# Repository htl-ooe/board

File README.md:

# HTL OOE HAT for Raspberry Pi
board schematic, layout and instructions on how to operate the board

## Installing the Operating System

### Downloading the Operating System
There are lots of operating Systems (Distributions) for the Raspberry Pi. Most of them are based on Linux.
The Foundation’s official supported operating system is [Raspberry Pi OS](https://www.raspberrypi.org/downloads/raspberry-pi-os/ "Raspberry Pi OS").
There are 3 Variants:
  * [Raspberry Pi OS with desktop and recommended software](https://downloads.raspberrypi.org/raspios_full_armhf_latest "Raspberry Pi OS full")
  * [Raspberry Pi OS with desktop](https://downloads.raspberrypi.org/raspios_armhf_latest "Raspberry Pi OS with Desktop")
  * [Raspberry Pi OS Lite (just Console, smallest in size)](hhttps://downloads.raspberrypi.org/raspios_lite_armhf_latest "Raspberry Pi OS Lite")

In our case [Raspberry Pi OS with desktop](https://downloads.raspberrypi.org/raspios_armhf_latest "Raspberry Pi OS with Desktop") is the the best choice.
You can not just copy the files to a Micro SD Card to install the Operating System. To boot Raspberry Pi OS you have to install the Operating System on the Micro SD Card.
Look at [Installing operating system images](https://www.raspberrypi.org/documentation/installation/installing-images/README.md "Installing operating system images") for how to do this. [balenaEtcher](https://www.balena.io/etcher/ "balena Etcher") installs itself to the Userprofile, take care of that when trying to use with different Accounts!
You will need administrative rights to format the Micro SD Card, so installing and using balena Etcher as Administrator is a good choice.
To be able to connect via ssh to the Raspberry Pi (headless) you can place the Files [ssh und wpa_supplicant.conf](https://www.raspberrypi.org/documentation/configuration/boot_folder.md "ssh und wpa_supplicant.conf") in the boot Folder of the Micro SD Card during the verify Cycle of  balena Etcher.
When using a SD Card to Micro SD Card Adapter, there is a Switch called **LOCK**. Take care, that the Switch is in the unlocked position (balena Etcher will tell you if the Micro SD Card is write protected).
When you access the Micro SD Card using Microsoft Windows, it asks for **formatting** the Device. **Don't do this!**
Now you can power up the Raspberry Pi with the plugged in Micro SD Card. If the Rasperry Pi is connected to a Monitor, you can you can read the Raspberry Pi's IP Address.
When you operate the Raspberry Pi headless you can use IP Scanners like the [Advanced IP Scanner](https://www.advanced-ip-scanner.com/ "Advanced IP Scanner") to get the IP Address.
Transfering Files is easy with [WinSCP](https://winscp.net/eng/download.php "WinSCP"). You can start a Terminal Program from within WinSCP itself or download [PuTTY](https://www.chiark.greenend.org.uk/~sgtatham/putty/latest.html "PuTTY").
When connected, you can enable **VNC** via
```console
pi@raspberrypi:~ $ sudo raspi-config
```
and use a Viewer like [VNC Viewer](https://www.realvnc.com/en/connect/download/viewer/ "VNC Viewer")

### Updating the Operating System and Installing Software

#### preparing APT for use with an Proxy
Create a new File called proxy.conf and edit it. You can use an Editor like **nano** or **vi**
```console
pi@raspberrypi:~ $ sudo touch /etc/apt/apt.conf.d/proxy.conf
pi@raspberrypi:~ $ sudo vi /etc/apt/apt.conf.d/proxy.conf
```
Add the following Lines to the empty File:
```code
Acquire {
  HTTP::proxy "http://proxy.htl-steyr.ac.at:8082/";
  HTTPS::proxy "https://proxy.htl-steyr.ac.at:8082/";
}
```
If you do not need the proxy (e.g. at home), you can just rename the File to disable the proxy:
```console
pi@raspberrypi:~ $ sudo mv /etc/apt/apt.conf.d/proxy.conf /etc/apt/apt.conf.d/proxy.conf.htl
```
#### Using APT
Using **apt-get** (Advanced Packaging Tool) you can update the Operating System and install Software.
The most important apt-get commands are:
| command | description |
| ----------- | ----------- |
| update | downloads the package lists from the repositories |
| upgrade | updates the list of available packages and their versions |
| install | installs one or more program package(s) |
| purge | removes a program package including the configuration|
apt-get needs the time and date to be set to an actual value! You can do this by typing
```console
pi@raspberrypi:~ $ sudo date -s "13 Jun 2020 09:20:00"
pi@raspberrypi:~ $ date # returns current time and date
```
If you have a ntp timeserver up and running you can edit
```console
pi@raspberrypi:~ $ sudo vi /etc/systemd/timesyncd.conf
```
to update the time via network.

To do the necessary software Maintenance you should enter
```console
pi@raspberrypi:~ $ sudo apt-get -y update && sudo apt-get -y dist-upgrade
```
Setting the Time Zone and enabling ntp (network time protocol)
```console
pi@raspberrypi:~ $ sudo timedatectl set-timezone Europe/Vienna
pi@raspberrypi:~ $ sudo timedatectl set-ntp true
```

## Device Tree
To manage ressources Linux uses the [Device Tree](https://www.raspberrypi.org/documentation/configuration/device-tree.md "Device Tree"). Parts of it are configured in the File [config.txt](https://www.raspberrypi.org/documentation/configuration/config-txt/README.md "config.txt").
You can also add devices via the EEPROM on a [HAT](https://github.com/raspberrypi/hats "HAT").
To configure devices [virtual Filesystems](https://en.wikipedia.org/wiki/Virtual_file_system "virtual Filesystems") (/dev, /sys, /proc) are frequently used.
### PWM
Our HAT uses PWM channels. The **root** user can access the onboard chanels.
If the user **pi** should use the pripheral, you have to give him the rights to do this:
Edit the File `/etc/udev/rules.d/99-com.rules`
```console
pi@raspberrypi:~ $ sudo vi /etc/udev/rules.d/99-com.rules
```
and change
```code
        chown -R root:gpio /sys/devices/platform/soc/*.pwm/pwm/pwmchip* && chmod -R 770 /sys/devices/platform/soc/*.pwm/pwm/pwmchip*\
```
to
```code
        chown -R root:gpio /sys/devices/platform/soc/*.pwm/pwm/pwmchip* && chmod -R 770 /sys/devices/platform/soc/*.pwm/pwm/pwmchip*;\
        chown -R root:gpio /sys/devices/platform/soc/*.i2c/i2c*/*/pwm/pwmchip* && chmod -R 770 /sys/devices/platform/soc/*.i2c/i2c*/*/pwm/pwmchip*\
```
mind the semicolon **;** to be added to the first Line!

Controlling the PWM Unit can be done in the virtual Filesystem `/sys/class/pwm/pwmchip*`.
When using **Python** [python-periphery](https://python-periphery.readthedocs.io/ "python-periphery") can access the PWM channels.
Keyboard, Mouse, Joysticks and Game Controllers can easily be accessed using [python-evdev](https://python-evdev.readthedocs.io/ "python-evdev")
#### Programing the HAT EEPROM
Download the latest Version of the **eepromutils** and compile the utils. You can also download the Repository (zip file) and unzip them in pi's homedirectory. Then you have to rename the directorys, so they do not contain "-master".
```console
pi@raspberrypi:~ $ sudo apt-get install -y git
pi@raspberrypi:~ $ git clone https://github.com/raspberrypi/hats.git
pi@raspberrypi:~ $ git clone https://github.com/htl-ooe/board.git
pi@raspberrypi:~ $ cd hats/eepromutils && make ; cd
```
```console
pi@raspberrypi:~ $ sudo dtc -@ -H epapr -O dtb -o "/boot/overlays/smartcar-V1-2.dtbo" -W no-unit_address_vs_reg './board/hat/smartcar-V1-2-overlay.dts'
```
compiles the device tree source file and copies it to `/boot/overlays`. You can test the overlayfile by adding the line
`dtoverlay=smartcar-V1-2` to [config.txt](https://www.raspberrypi.org/documentation/configuration/config-txt/README.md "config.txt")
```console
pi@raspberrypi:~ $ ./hats/eepromutils/eepmake ./board/hat/eeprom_settings-V1-2.txt ./board/hat/smartcar-V1-2.eep /boot/overlays/smartcar-V1-2.dtbo
```
generates the contents of the EEPROM

Disable the write protection with a piece of wire or calipers: 

```console
pi@raspberrypi:~ $ sudo ./hats/eepromutils/eepflash.sh -w -f=./board/hat/smartcar-V1-2.eep -t=24c512
```
writes smartcar-V1-2.eep to the EEPROM, assumed that you disabled the Write Protection and i2c-0 can be enabled. Propably you need dtparam=i2c_vc=on in [config.txt](https://www.raspberrypi.org/documentation/configuration/config-txt/README.md "config.txt").

#### Reboot
```
pi@raspberrypi:~ $ sudo reboot
```

## Ultrasonic Sensors
### Compile modules install toolchain and headers
```console
pi@raspberrypi:~ $ sudo apt-get install -y raspberrypi-kernel-headers
```
installs the header Files for the Kernel
```console
pi@raspberrypi:~ $ git clone https://github.com/htl-ooe/board.git
pi@raspberrypi:~ $ sudo /home/pi/board/drivers/install.sh
```
compiles the srf04.c File and copies it to the propper directory. When you did this once you can copy the compiled module to another Raspberry Pi and do not have to compile (download the rpi headers) again.
## IR Receiver
install ir-keytable
```console
pi@raspberrypi:~ $ sudo apt-get install -y ir-keytable
```
select the desired Protocol (templates: /lib/udev/rc_keymaps) eg: rc6_mce
```console
pi@raspberrypi:~ $ sudo ir-keytable -p rc-5,rc-5-sz,jvc,sony,nec,sanyo,mce_kbd,rc-6,sharp,xmp -w /lib/udev/rc_keymaps/rc6_mce.toml
```
to test type
```console
pi@raspberrypi:~ $ ir-keytable --test
```
to bind actions (triggers) to a IR Key edit eg. /etc/triggerhappy/triggers.d/power.conf (new File)
and add the line **KEY_POWER		1	sudo /sbin/halt** to shutdown with the power key

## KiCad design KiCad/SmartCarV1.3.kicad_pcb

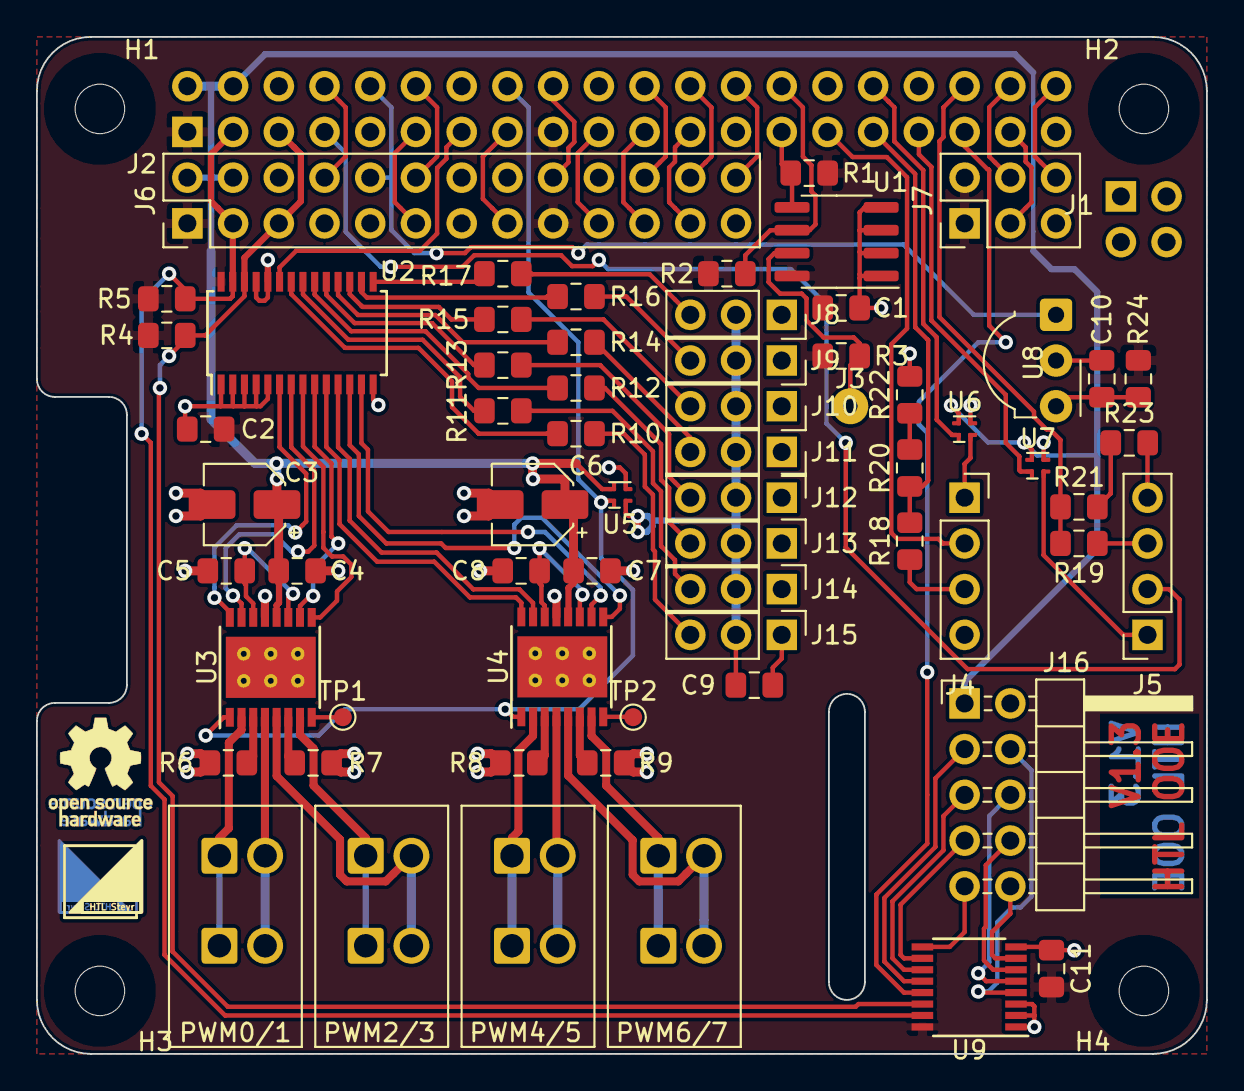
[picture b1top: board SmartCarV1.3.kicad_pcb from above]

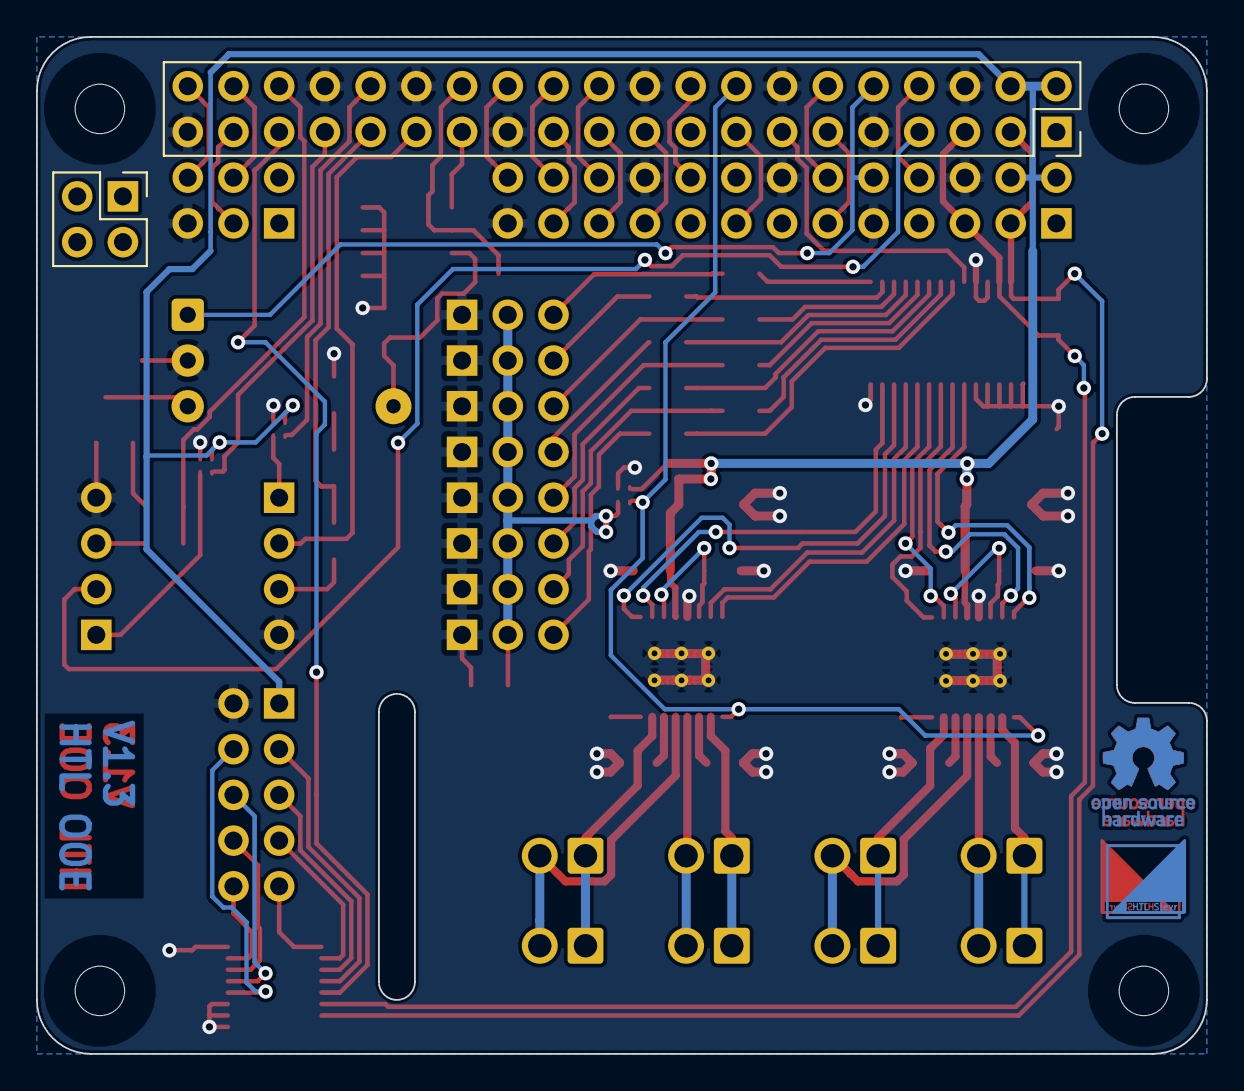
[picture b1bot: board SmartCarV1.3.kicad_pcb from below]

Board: 2 copper layers, 65.0 x 56.5 mm, 76 parts (4 on the bottom side), 88 nets.

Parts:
C1, C2, C4, C7, C9, C10, C11: 100nF; C_0805_2012Metric_Pad1.15x1.40mm_HandSolder
C3, C6: 10uF; CP_Elec_4x5.7
C5, C8: 2,2uF; C_0805_2012Metric_Pad1.15x1.40mm_HandSolder
H1, H2, H3, H4: MountingHole; MountingHole_2.7mm_M2.5
J1: PI4HAT; PinSocket_2x02_P2.54mm_Vertical
J2: PI40HAT; PinSocket_2x20_P2.54mm_Vertical
J3: Conn_01x01; SolderWirePad_1x01_Drill0.8mm
J4, J5: Conn_01x04; PinSocket_1x04_P2.54mm_Vertical
J6: Conn_02x13_Odd_Even; PinHeader_2x13_P2.54mm_Vertical
J7: Conn_02x03_Odd_Even; PinHeader_2x03_P2.54mm_Vertical
J8, J9, J10, J11: Conn_01x03; PinSocket_1x03_P2.54mm_Vertical
J12, J13, J14, J15: Conn_01x03; PinHeader_1x03_P2.54mm_Vertical
J16: Conn_02x05_Odd_Even; PinHeader_2x05_P2.54mm_Horizontal
Logo1, Logo3: HTL-Steyr-Logo_4x4mm_Copper
Logo2, Logo6: OSHW-Logo_5.7x6mm_Copper
Logo4: HTL-Steyr-Logo_4x4mm_SilkScreen
Logo7: OSHW-Logo_5.7x6mm_SilkScreen
PWM0/1, PWM2/3, PWM4/5, PWM6/7: Conn_01x02; TE_2834085-1_1x02_P2.54mm_45deg
R1, R2, R3, R4, R5, R18, R19, R20, R21, R22, R23: 3k9; R_0805_2012Metric_Pad1.15x1.40mm_HandSolder
R6, R7, R8, R9: 470m; R_0805_2012Metric_Pad1.15x1.40mm_HandSolder
R10, R11, R12, R13, R14, R15, R16, R17: 270; R_0805_2012Metric_Pad1.15x1.40mm_HandSolder
R24: 100; R_0805_2012Metric_Pad1.15x1.40mm_HandSolder
TP1, TP2: TestPoint_Probe; TestPoint_Pad_D1.0mm
U1: CAT24C512; SOIC-8_3.9x4.9mm_P1.27mm
U2: PCA9685PW; TSSOP-28_4.4x9.7mm_P0.65mm
U3, U4: DRV8848; HTSSOP-16-1EP_4.4x5mm_P0.65mm_EP3.4x5mm_Mask2.46x2.31mm_The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
U5, U6, U7: MIC94044YFL; MLF-4-1.2x1.2mm
U8: TSOP43xx; Vishay_MOLD-3Pin
U9: TCA9554DBQ; SSOP-16_3.9x4.9mm_P0.635mm

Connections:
+3V3: C1.1, C2.1, C11.2, J2.1, J2.17, J6.1, J6.17, J7.1, J7.2, R1.2, R2.2, R3.2, R4.2, R5.2, R24.1, U1.8, U2.28, U9.16
+5V: C3.1, C4.1, C6.1, C7.1, J2.2, J2.4, J6.2, J6.4, J16.1, U3.12, U4.12, U5.3, U6.3, U7.3
/GPIO04: J2.7, J5.2
/GPIO05: J2.29, J4.2
/GPIO06: J2.31, R18.2, R20.1
/GPIO07: J2.26, J6.26
/GPIO08: J2.24, J6.24
/GPIO09: J2.21, J6.21
/GPIO10: J2.19, J6.19
/GPIO11: J2.23, J6.23
/GPIO12: J2.32, U6.4
/GPIO13: J2.33, U7.4
/GPIO14: J2.8, J6.8
/GPIO15: J2.10, J6.10, U8.1
/GPIO16: J2.36, R19.2, R21.1
/GPIO17: J2.11, J6.11
/GPIO18: J2.12, J6.12
/GPIO19: J2.35, U9.13
/GPIO20: J2.38, J7.4
/GPIO21: J2.40, J7.6
/GPIO22: J2.15, J6.15
/GPIO23: J2.16, U3.1, U4.1, U5.4
/GPIO24: J2.18, J6.18
/GPIO25: J2.22, J6.22
/GPIO26: J2.37, J7.3
/GPIO27: J2.13, U2.23
/ID_SC_EEPROM: J2.28, R2.1, U1.6
/ID_SD_EEPROM: J2.27, R1.1, U1.5
/SCL1: J2.5, J6.5, R4.1, U2.26, U9.14
/SDA1: J2.3, J6.3, R5.1, U2.27, U9.15
GND: C1.2, C2.2, C3.2, C4.2, C5.2, C6.2, C7.2, C8.2, C9.2, C10.1, C11.1, J2.6, J2.9, J2.14, J2.20, J2.25, J2.30, J2.34, J2.39, J4.4, J5.4, J6.6, J6.9, J6.14, J6.20, J6.25, J7.5, J8.1, J9.1, J10.1, J11.1, J12.1, J13.1, J14.1, J15.1, J16.2, R6.2, R7.2, R8.2, R9.2, R22.2, R23.2, U1.1, U1.2, U1.3, U1.4, U2.1, U2.2, U2.3, U2.4, U2.5, U2.14, U2.24, U2.25, U3.13, U3.17, U4.13, U4.17, U5.2, U6.2, U7.2, U8.2, U9.1, U9.2, U9.3, U9.8
unnamed: C5.1, U3.11, U3.14
unnamed: C8.1, U4.11, U4.14
unnamed: C9.1, J8.2, J9.2, J10.2, J11.2, J12.2, J13.2, J14.2, J15.2, U5.1
unnamed: C10.2, R24.2, U8.3
unnamed: J3.1, R3.1, U1.7
unnamed: J4.1, U6.1
unnamed: J4.3, R18.1
unnamed: J5.1, U7.1
unnamed: J5.3, R19.1
unnamed: J8.3, R17.1
unnamed: J9.3, R16.1
unnamed: J10.3, R15.1
unnamed: J11.3, R14.1
unnamed: J12.3, R13.1
unnamed: J13.3, R12.1
unnamed: J14.3, R11.1
unnamed: J15.3, R10.1
unnamed: J16.3, U9.12
unnamed: J16.4, U9.4
unnamed: J16.5, U9.11
unnamed: J16.6, U9.5
unnamed: J16.7, U9.10
unnamed: J16.8, U9.6
unnamed: J16.9, U9.9
unnamed: J16.10, U9.7
unnamed: PWM0/1.1, U3.2
unnamed: PWM0/1.2, U3.4
unnamed: PWM2/3.1, U3.7
unnamed: PWM2/3.2, U3.5
unnamed: PWM4/5.1, U4.2
unnamed: PWM4/5.2, U4.4
unnamed: PWM6/7.1, U4.7
unnamed: PWM6/7.2, U4.5
unnamed: R6.1, U3.3
unnamed: R7.1, U3.6
unnamed: R8.1, U4.3
unnamed: R9.1, U4.6
unnamed: R10.2, U2.22
unnamed: R11.2, U2.21
unnamed: R12.2, U2.20
unnamed: R13.2, U2.19
unnamed: R14.2, U2.18
unnamed: R15.2, U2.17
unnamed: R16.2, U2.16
unnamed: R17.2, U2.15
unnamed: R20.2, R22.1
unnamed: R21.2, R23.1
unnamed: TP1.1, U3.8
unnamed: TP2.1, U4.8
unnamed: U2.6, U3.16
unnamed: U2.7, U3.15
unnamed: U2.8, U3.9
unnamed: U2.9, U3.10
unnamed: U2.10, U4.16
unnamed: U2.11, U4.15
unnamed: U2.12, U4.9
unnamed: U2.13, U4.10

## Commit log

2020-06-13 Add board schematics, layout and testprogram
2020-06-13 typo
2020-06-17 added missing instruction for cloning the repo, and for the EEPROM write protection
2020-06-17 add required reboot instruction
2020-06-23 add hint to dtoverlay=smartcar-V1-2
2020-09-30 Add more gpio ports for switches, leds, etc.
2020-10-27 Update smartcar-V1-3-overlay.dts
    correct Version number
2020-10-27 Update README.md
    make eeprom_settings version dependent
2020-10-27 Rename eeprom_settings.txt to eeprom_settings-V1-2.txt
2020-10-27 Update README.md
    add /etc/systemd/timesyncd.conf NTP configuration
2020-10-27 Update README.md
    add git clone https://github.com/htl-ooe/board.git to Ultrasonic Sensors section
2021-03-14 remove pinctl fron ultrasonic sensors, add pin-names to motor driver
